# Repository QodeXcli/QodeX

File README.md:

# QodeX — the coding agent that stays on your side of the glass

Most agent CLIs are a rented brain with a terminal skin. QodeX is the opposite: a **local-first agentic coding CLI** that treats *your* machine as the source of truth. Qwen3-Coder on Ollama / LM Studio by default. Claude / GPT / Gemini / DeepSeek only if you invite them. Your repo does not become someone else's training set.

It does not just *chat about* code. It reads, edits, tests, and — if you ask — ships. And when you are not at the desk, it does not get the keys to the whole Mac: **shell can run in a Docker sandbox**, and **`--profile cloud`** is one switch between "think local" and "think in the cloud, execute in a box."

> Looking for an **LLM agent**, a **CLI agent**, or an **autonomous terminal agent** that can go fully offline? That's QodeX.

```bash
curl -fsSL https://raw.githubusercontent.com/QodeXcli/QodeX/main/install.sh | bash
qodex setup && qodex
```

**Version 2.33.0** · 100+ tools · self-improving · phone-driveable · English & Persian · Apache-2.0

---

## Highlights

- **Local-first & private** — runs entirely on *your* models (Qwen-Coder via Ollama / LM Studio); your code never leaves the machine. Claude / GPT / Gemini / DeepSeek are opt-in cloud fallbacks.
- **A desk on this machine, not a rented computer** — `qodex desk` is a local team of up to six that can run at once and share `~/.qodex/desks/computer`. A goal that would send, spend, delete, publish, or touch a secret waits for `qodex desk allow`. If the run then tries that call, the sentinel pauses the exact tool until `qodex desk allow-call`, and then it runs. Click and type work on macOS, on Linux with xdotool, and on Windows via PowerShell. `qodex desk teach --from-last` saves the tools the run actually used. [docs/DESK.md](docs/DESK.md).
- **One process you leave up** — `qodex up` fires schedules, drains runnable desks, seals a skill only when its witness patch still passes the real checker (no model), and attaches the chat bots you already configured. `qodex up status` says whether that pid is alive. `--once` is a single pass and does not open bots.
- **Named desktop controls** — `computer_use_tree` reads the OS accessibility tree (macOS AX, Windows UI Automation, Linux AT-SPI). `computer_use_invoke` presses one named control, refuses zero or two matches, and reads the tree again. If the control still looks the same, the result is unverified. A missing backend is an error, not a fake click.
- **Desktop shell** — `qodex desktop` prefers a native OS window (`native/`, built with `qodex desktop --build-native`). That window is not a browser. If the binary is missing it says so and falls back to Chrome/Chromium/Edge `--app`, or a tab. Loopback only. You read the real control tree, press or fill one name, and take a screenshot. It does not call a model.
- **Cloud browser, your account** — `qodex mcp add browserbase` connects to Browserbase's hosted server. The API key stays in the environment. `start` and `act` ask every time, because a session is billed and a click can submit. No key, no browser — the call errors.
- **`--profile studio` / `--profile cloud`** — named overlays, not a second product. Local Qwen on the Mac Studio in one file; a cloud model + Docker-isolated shell in another. `-p` is still `--print`.
- **Shell in a box, not on bare metal** — `runtime.backend: docker` bind-mounts the project and drops host `$HOME`, `docker.sock`, privileged mode, and host networking. File edits stay in the repo (a coding agent that cannot touch files is a chatbot). The Mac outside `/workspace` stays out of reach.
- **Guardrails around the model, not just prompts** — a syntax gate, completion gate, and per-language auto-verification run *around* the agent loop, so even a weak local model **can't ship broken or unverified code**.
- **It gets sharper the more you use it** — a real self-improvement loop captures the winning approach from *objectively-successful* tasks as quarantined skills. An **independent judge model** can promote them when you have a second model. On one local model (the default), **witnessed replay** re-applies the exact diff in a clean worktree and lets the compiler decide — `qodex skill witness`, no self-grade. **UCB1 A/B-tests** champion vs. challenger versions, **episodic memory** recalls how you solved similar tasks before, and it **learns from recurring failures**. It never overwrites a skill you wrote. Gap vs Hermes Agent: [docs/VS-HERMES.md](docs/VS-HERMES.md).
- **Always reachable — drive it from your phone** — run QodeX as a **Telegram / Discord / Slack service** and command the *same* agent from chat: stream tasks, approve diffs as inline buttons, and get **Living Artifacts** back as cards with an AI **vision review** (looks-good / needs-work / broken) and Approve / Edit / Reject.
- **Remembers across sessions** — a layered, **local** memory (curated `QODEX.md` rules · scoped project/user facts · per-project worklog · episodic task-recall · resumable sessions) with a **human-readable Markdown mirror** you can edit and git-commit, and a **budget-aware Light Memory Mode** for small context windows. The agent builds real context about *you* and *this* codebase instead of starting every session cold.
- **Live, shareable artifacts + a project dashboard** — build a page / React app / dashboard that **hot-reloads on every edit and auto-opens in your browser**; share it over your LAN or a private, token-protected https tunnel. `qodex dashboard` renders a live snapshot of providers, sessions, token/cost, memory, and skills.
- **Design and account connectors** — **Canva** and **Figma** were already one command. 2.12 adds the official Google servers (Gmail, Drive, Calendar, Docs, Sheets), Hotmail / Outlook, Notion, and Jira / Confluence. Each one is the vendor's real server. Nothing is simulated.
- **100+ built-in tools** — Tree-sitter code-graph, real Playwright browser automation, dev-servers, web search, vision, Docker / DB / WordPress, and any MCP server.
- **Persian-first** — prompts, skill matching, *and* generated artifact copy follow your chat language, not a fixed default.
- **Token-efficient** — sub-agent delegation, result-aging, compaction, and tool-gating keep the working context small on long sessions.

---

## Always-on, and it compounds

An "autonomous 24/7 agent" is easy to *say* and hard to *mean* — most of the time it's a chatbot wrapped in a cron job. QodeX's always-on story is three systems that actually exist, that you can read in this repo, and that each have tests:

- **Reachable any time** — the **transport-agnostic bot gateway** runs as a persistent service, so the agent is one message away from your phone. One turn per chat at a time (no interleaving), permission prompts as inline buttons, **deny-by-default auth**. ([Telegram / Discord / Slack](#telegram--discord--slack-bot))
- **Improves between sessions, on its own** — capture → **independent-judge** promotion → **UCB1** version A/B → **episodic recall** → **failure-lesson** injection. The loop is gated on *objective* success signals, not the model's self-grade, and a new **code-graph "fit" signal** grounds the judge in *your* codebase. ([Self-learning skills](#self-learning-skills))
- **Runs while you sleep — verifiably** — a built-in **cron scheduler** (launchd / crontab) runs tasks unattended and delivers the result to your phone. The headline recipe, **Autonomous Verified PR**, works on a sandbox branch, **verifies**, and opens a PR *only if it passed* — per-task **budget caps**, a **circuit breaker**, the **git sandbox**, and the guardrail gates all run too, so a 3am run **can't quietly ship broken code or melt your token budget**. ([Scheduled & autonomous](#scheduled--autonomous--the-real-247))

We're not going to claim a model thinks for you around the clock. We built the parts that make *unattended, repeated, real* work trustworthy — and we'd rather show the code than the slogan.

---

## What makes it different

Most agentic CLIs *delegate to the model* — they hand the model tools and trust it to use them well. That works with a frontier model and falls apart with a weaker local one (loops, half-finished edits, "done" when nothing was tested).

QodeX takes the opposite stance: **protect the model.** A layer of deterministic guardrails runs *around* the loop so even a smaller local model produces trustworthy output:

- **Syntax gate** — every edit is parsed before it's written; broken syntax is rejected, not saved.
- **Completion gate** — the model can't claim "tests pass" or "I fixed it" unless a test actually ran / an edit actually succeeded. Unsupported claims get bounced back for correction.
- **Auto-verification** — after the model thinks it's done, QodeX detects the project type and runs the real checker (`tsc`, `eslint`, `ruff`, `pyright`, `go vet`, `cargo`, `php -l` …) on touched files and force-feeds any errors back.
- **Interactive edit approval** — see a red/green diff and Accept / Edit / Continue / Reject before anything hits disk (or `/auto on` to skip).
- **Git-backed sandbox** — risky work runs on a hidden branch with checkpoints; auto-snapshot (`git stash`) before destructive commands, one command to roll back.
- **Process sandbox (Docker)** — a second, different isolation: the *shell* runs in a container so a remote-ish turn cannot `rm` your home directory. Pair it with `--profile cloud`. Not a Hub client — Hub is for approvals; this is where commands actually execute.
- **Skill security scanner** — skills installed from GitHub are scanned for prompt injection, secret exfiltration, destructive shell, and hidden-unicode payloads *before* they touch disk.

The result raises the **floor** (what a weak model is allowed to ship) without needing a bigger model.

## Token efficiency

Long agent sessions burn tokens on a growing history, not the (cached) system prompt. QodeX keeps the working context small with four real levers:

- **Delegation** — heavy file-exploration runs in a read-only sub-agent (`task`) with a *separate* context window; only its summary returns, so dozens of reads never pile up in the main window.
- **Result-aging** — stale large tool outputs are stubbed after a few turns (re-read on demand).
- **Compaction** — history is structured-summarized as the window fills.
- **Tool-gating** — only relevant tool schemas are sent each turn (a greeting sees ~20 tools, a real task ~50, out of 100+).
- **Opt-in `context.efficient: true`** tightens all of the above for weak local models — a **sliding token window** that compresses large tool outputs the very next turn.

### Hierarchical cache engineering

Standard agent caching pins only the static system block. QodeX goes further with a **multi-tier rolling-breakpoint** cache (Anthropic, on by default), so the part that actually grows — the conversation — is cached too:

- **Immutable tier** — core instructions + 70+ tool schemas, byte-identical across *every turn of the session*. A static/volatile boundary splits the system prompt so this core gets its own breakpoint and stays a cache **hit** the whole conversation — not just within one task.
- **Ephemeral / rolling tier** — per-turn injections (memory, retrieval, dir-tree) and the conversation history, pinned with a **breakpoint that advances every turn**.

In a deep agentic loop the re-sent prefix dominates each call, and it's now served at **0.1×** instead of full price — **up to ~90% off the input cost of every iteration after the first** (the `C × N` blow-up, defused) — with no loss of granular state and no shrinking of the context window. Caching the *growing history*, not just the system block, is the lever; opt out with `providers.anthropic.useCaching: false`.

A live `12.4k/200k ████░░░░░░ 8%` meter in the status bar shows how full the context window is.

## What it can do

Give QodeX a task in natural language (English or Persian) and it drives a real agent loop:

- **Read and edit code** — `read_file`, `write_file`, `edit_text`, `edit_symbol` (AST-aware), `multi_edit` (single-file sequential), `multi_file_edit` (atomic across up to 50 files).
- **Understand a codebase** — `ls`, `glob`, `grep`, plus a Tree-sitter code-graph: `project_overview`, `analyze_impact`, `find_callers`, `find_references`, `find_dead_code`, `safe_rename`.
- **Run commands** — `shell` on the host, or inside Docker when `runtime.backend: docker`; plus `code_run` for sandboxed Python / Node / TS / PHP / Ruby (macOS `sandbox-exec` where available).
- **Drive a real browser** — Playwright-backed Chromium: navigate, click, fill, screenshot, evaluate JS, read console + page errors — to verify your own UI changes. Click, fill, and page script ask every time. A standing yes does not cover them.
- **Manage dev servers & jobs** — `dev_server_start npm run dev` then `browser_navigate http://localhost:5173`; `background_job_start` for async work, all in one session.
- **Search the web** — DuckDuckGo by default (hardened with a `lite` fallback + retry), or Tavily / Brave / **Firecrawl** (returns full page markdown inline to save round-trips) when you set a key. Auto-fallback chain across whatever keys are present.
- **Smart vision** — `vision_analyze` automatically uses *your own* vision-capable model (Gemini, GPT‑4o, Claude, or a local Qwen‑VL) when your primary or sub‑agent can already see; it only spins up a dedicated vision model when neither can.
- **Shareable live artifacts** — build a web page / React / dashboard and serve it with `artifact_live` that **hot‑reloads on every edit and auto‑opens in your browser** so you watch it change live; `share="network"` opens it to your LAN and `share="tunnel"` gives a **private https link your team can open** (token‑protected) — a live PR walkthrough or project dashboard.
- **Design integrations (Figma + Canva)** — `qodex mcp add figma` (3 ways: your logged‑in desktop Dev Mode, a personal token, or hosted OAuth) and `qodex mcp add canva` (OAuth login) let the model turn a Figma frame into code or build a Canva design — driven from the terminal over MCP.
- **Google, Hotmail, Notion, Jira** — `qodex mcp add gmail` (also `google-drive`, `google-calendar`, `google-docs`, `google-sheets`), `hotmail`, `notion`, `atlassian`. Google's servers are the official `*mcp.googleapis.com` endpoints. They are a developer preview: you create the OAuth client (marked "Use this client for an AI-powered agent") and export `GOOGLE_OAUTH_CLIENT_ID` / `GOOGLE_OAUTH_CLIENT_SECRET`. Gmail's server searches and drafts; it does not send. Hotmail is `@softeria/ms-365-mcp-server` in personal mode (device code). Work tenants are `outlook-work`. Canva was already `qodex mcp add canva`.
- **Matches your code style automatically** — QodeX infers the project's conventions (indentation, quotes, semicolons, naming) from its own source + `.editorconfig` and writes new code to match, **without you having to configure or `remember` anything**. Off via `context.styleProfile: false`.
- **Self‑learning skills** — after a task that *objectively* succeeded (verified + honest, ≥ a few tool calls), QodeX can capture the winning approach as a **candidate** skill in quarantine. An **independent judge model** (a *different* model from the one that did the work) reviews it before it’s promoted, and a human‑authored skill is **never** overwritten. Drive it with `qodex skill candidates | curate | promote`. Off by default (`learning.enabled`).
- **Trade‑off & business analysis** — ask it to analyze or plan (not code) and it produces **decision‑grade output**: options × weighted criteria → a scored comparison and one clear recommendation, business‑plan structure, no invented numbers.
- **Persian‑first** — skill auto‑loading and tool selection understand Persian prompts (تحلیل، دیتابیس، آرتیفکت…), not just English keywords.
- **Verify its own work** — `auto_fix` runs your test command in a fix→test loop with an iteration cap and same-failure-twice detection; the auto‑verify gate runs the right checker **per language** in a polyglot repo (TS *and* Python both get checked).
- **Git** — status, diff, log, branch, commit, create-pr, release-notes.
- **Skills** — install from a curated registry or any GitHub repo (single / multi / catalog), security-scanned on the way in; `search_skills` to find them.
- **Sub-agents & orchestration** — `task` delegates to a separate model/window; `orchestrate` runs a DAG of sub-agents; `gather` fans out reads in parallel.
- **MCP** — connect any MCP-compatible server; its tools join the same registry as built-ins.
- **Live control dashboard** — `qodex dashboard` (alias `dash`) opens a **local, token-protected control panel** (127.0.0.1 only) that doesn't just *show* your QodeX — providers, sessions, token/cost, memory, skills — it **drives** it: toggle prompt caching / efficient mode / memory mode / sub-agents / learning, enable·disable·remove **scheduled tasks**, forget a memory fact, and apply MoE **offloading** — changes hit your real config and stores. Every capability is one entry in an action registry, so the panel grows to cover all of QodeX. `--static` writes the old read-only HTML snapshot.
- **Add a provider by just asking** — tell QodeX *"add Groq with my key"* and the `add_provider` tool wires the gateway into `~/.qodex/config.yaml` (key stays in `~/.qodex/.env`, never the config); or run `qodex provider add` for a guided setup. Unknown providers are refused unless you give a base URL + key-env, so nothing is silently misconfigured.
- **Domain tools** — Docker, databases, WordPress (`php -l` linting), media (ffmpeg), frontend/print, OpenAPI digest, and more.

## Self-learning skills

QodeX can **learn reusable playbooks from your successful tasks** — without the usual failure mode of an agent rubber-stamping its own work and overwriting your hand-tuned skills. The whole loop is **off by default** and gated on *objective* signals, not the model's self-grade.

**How it works:**

1. **Capture** — when a task finishes in the git sandbox and *objectively* succeeds (it compiled / type-checked, the completion-claim gate passed, and it took at least a few tool calls and changed a file), QodeX distills the winning approach into a `SKILL.md` and assigns it a **confidence score (0–100)** from those objective signals.
2. **Quarantine** — the new skill is written to `~/.qodex/skills-candidates/` (a dir QodeX never auto-loads), stamped `provenance: machine`, `status: candidate`. It can't affect the model until promoted.
3. **Independent review** — `qodex skill curate` runs an **independent judge model** (a *different* model from the one that did the work — a self-grade is refused) against a fixed rubric (reusable / correct / specific / non-redundant). The judge is **grounded in your codebase**: a Tree-sitter **code-graph "fit" signal** checks how many of the symbols a candidate references actually exist here, so a skill that name-drops APIs your project doesn't have scores lower (and the capture notice shows it: *"confidence 82/100 · codebase-fit 90%"*). Near-duplicate candidates are **merged** into one. It **never overwrites a human-authored skill**, and snapshots the skills dir (`tar.gz`) before any change so you can roll back.
4. **Auto-evaluation** — `qodex skill eval <name>` (or `learning.autoEval` to run it right after capture) **replays the skill's original task in a throwaway git worktree** and runs the **real** verifier (`tsc`/`ruff`/…) on the code it produces, recording **pass / fail / inconclusive** into the skill. It tests whether the skill actually *works*, not just whether a judge likes it. Content-hash cached.
5. **Learning from failures** — with `learning.failureLessons.enabled`, QodeX records tool failures and, once a mistake **recurs across tasks**, injects a deterministic "learned caution" into the prompt (e.g. *"verify a symbol exists before `edit_symbol`"*) so it stops repeating it. One-offs never teach; see `qodex skill lessons`.
6. **Episodic memory** — with `learning.episodicMemory.enabled`, QodeX records a lean episode after each successful task and, at the start of a new one, recalls **similar past tasks on this project** and injects a one-line reminder of what worked — so it reuses its own approach instead of rediscovering it. Retrieval is **smart, not noisy**: an unrelated task recalls nothing, and the top-K are selected for **relevance *and* diversity** (MMR — so a recurring task doesn't inject K copies of itself), **grounded** against the current tree (episodes pointing at files that no longer exist are demoted, like the skill-judge's codebase-fit), with a **recency tie-break** toward your more recent solution.

QodeX also **auto-matches your code style** (indentation, quotes, semicolons, naming — inferred from the project + `.editorconfig`) so generated code blends in without you having to spell it out. Off via `context.styleProfile: false`.

```yaml
# ~/.qodex/config.yaml — opt in
learning:
  enabled: true                     # capture candidates after successful tasks
  minToolCalls: 5                   # how substantial a task must be to capture
  judgeModel: llama-3.3-70b-versatile   # the INDEPENDENT judge (must differ from defaults.model)
  autoPromoteMinConfidence: 50      # hold lower-confidence captures for human review
  autoEval: false                   # run `skill eval` automatically after each capture
  failureLessons:
    enabled: true                   # learn from RECURRING tool failures
  episodicMemory:
    enabled: true                   # recall similar past tasks and reuse what worked
    topK: 2                         # how many past episodes to inject
    diversity: 0.3                  # 0–1: keep the top-K distinct, not K clones of one task
```

**A worked example.** With `learning.enabled` + an independent `judgeModel`, a typical loop:

```text
> add cursor pagination to the /orders endpoint        # you give a task
… QodeX edits, type-checks, tests, and the sandbox merges (objective success) …
🎓 Captured candidate skill "add-cursor-pagination" (confidence 82/100)
🧪 Auto-eval of "add-cursor-pagination": pass            # (if learning.autoEval)

$ qodex skill candidates        # review the quarantined capture
$ qodex skill curate            # an INDEPENDENT judge promotes/merges the good ones
$ qodex skill stats             # captured 3 · promoted 2 · promotion rate 67%

# next week, a similar task:
> add pagination to the /users endpoint
# → QodeX recalls the past episode + loads the promoted skill automatically.
```

```bash
qodex skill candidates          # list quarantined captures (with confidence)
qodex skill curate              # independent judge merges + promotes the good ones
qodex skill eval <name>         # replay the skill in a clean worktree + real verify → pass/fail
qodex skill promote <name>      # promote one yourself (you are the independent reviewer)
qodex skill reject <name>       # discard a candidate
qodex skill stats               # learning metrics: captured / promoted / merged, promotion rate, avg confidence
qodex skill lessons             # cautions learned from your recurring failures
qodex skill snapshots           # rollback points;  qodex skill restore <archive>  to roll back
```

> Every successful task can also be exported as a **ShareGPT JSONL** corpus (`flywheel.datasetExport: true` → `~/.qodex/dataset/`) — a ready-to-use dataset for a future zero-cost local fine-tune. Strictly local; nothing is uploaded.

### Skill versioning & A/B testing (UCB1)

A skill keeps its whole history in **one flat directory** — `manifest.json` + `SKILL.v1.md`, `SKILL.v2.md`, … — no symlinks, identical on every OS. When a new candidate is captured for an existing skill it becomes a **challenger** to the stable **champion**, and QodeX routes traffic between them with the **UCB1 adaptive bandit** instead of a fixed split: it explores the challenger enough to get signal, then favours whichever has the higher score — and a challenger that turns out worse has its traffic driven to **zero automatically**.

The score is a **composite reward**, not just win-rate: *success* dominates, but *token-* and *time-efficiency* (normalized **relative to the champion**) break ties — so between two equally-correct versions, the **cheaper, faster** one wins.

```yaml
learning:
  versioning:
    strategy: ucb1                 # or 'champion-only' to freeze a sensitive skill (UCB off)
    ucbExplorationFactor: 1.41     # √2 — higher explores challengers more
    minChallengerTrials: 5         # force a challenger ≥5 runs before judging it
    rewardWeights: { success: 0.7, token: 0.15, time: 0.15 }
```

```text
$ qodex skill versions git-commit-expert
Skill "git-commit-expert"  ·  strategy: ucb1  ·  routed this turn → v2

  v1  [human]   ★ champion
      success: 88% over 40  ·  tokens: 60000  ·  1900ms/run  ·  confidence: 75
      UCB: reward 0.838 + bonus 0.214 = 1.052
  v2  [machine] ⚡ challenger
      success: 92% over 12  ·  tokens: 41000  ·  1300ms/run  ·  confidence: 60
      UCB: reward 0.921 + bonus 0.391 = 1.312     ← higher → gets this turn

$ qodex skill rollback git-commit-expert v1     # snap the champion back to v1 anytime
```

## Memory & continuity

Most CLI agents are amnesiac — every session starts from a blank slate and you re-explain the same things. QodeX **remembers**, across five layers that each answer a different question, so a model on *your* machine accumulates real context about you and your codebase over time:

| Layer | Answers | Where it lives | Author |
|---|---|---|---|
| **Curated rules** | "What are the rules here?" | `QODEX.md` in the repo + `~/.qodex/QODEX.md` (global) | **you** — version-controlled, authoritative |
| **Learned facts** | "What did I learn about this codebase / this user?" | `session_facts` in `~/.qodex/sessions.db`, scoped `project` (per-cwd) or `user` (global) | the **agent**, mid-task |
| **Project worklog** | "What's been done here lately?" | `project_worklog` (per-cwd) | the agent + `/project log` |
| **Episodic memory** | "How did I solve a task like this before?" | `~/.qodex/episodes/*.jsonl` | the agent, after a *verified* success |
| **Sessions** | "Pick up exactly where we left off." | `sessions` + `messages` in `sessions.db` | every turn — `/resume <id>` |

The split is **deliberate**: *your* curated rules (`QODEX.md`, git-tracked) stay separate from the *agent's* auto-learned scratchpad (the DB) — no machine write ever touches your authoritative file, and there are no merge conflicts. Facts are **scoped** — a `project` fact (a build command, a gotcha) is auto-injected only when you start in that directory; a `user` fact (*"prefers Persian comments"*, *"always run tests before saying done"*) follows you into **every** project. Recall is smart, not heavy: episodic memory injects only relevant, **de-duplicated** past tasks above a threshold (an unrelated task recalls nothing) — a one-line reminder, never a full transcript.

**A Markdown mirror you can read, edit, and git-commit.** `/memory export` writes the agent's learned facts to a human-readable `MEMORY.md` (project) and `~/.qodex/memory.md` (user). Edit them by hand — fix a wrong fact, add three — and `/memory import` folds your changes back into the DB (additive). The DB stays the source of truth; the Markdown is the window into it.

**Light Memory Mode for small context windows.** On a roomy model, every fact is injected (`memory.mode: full`). On a tight local model, set `memory.mode: lightweight` (or `auto`) — QodeX injects your `!important`-tagged facts plus as many recent ones as fit a token budget, and leaves the rest to load on demand. Your memory doesn't shrink; only what's *pushed into each prompt* does.

**Searchable memory (FTS5).** As facts pile up, dumping the newest N isn't enough — `recall query="deploy key"` does a **relevance-ranked full-text search** (SQLite FTS5) over your facts and pulls out the specific one, so the agent finds an old gotcha instead of rediscovering it. This is the on-demand half of Light Memory Mode: lightweight mode keeps prompts small, and search retrieves anything it left out. The index stays in sync automatically and falls back to a substring scan if a build lacks FTS5.

```text
> the build here is `npm run build:prod`, not `npm run build`
🧠 remembered (project)              # silently re-injected next time you start in this dir

/memory                              # show what's stored for this project
/memory export                       # write the human-readable MEMORY.md mirror
/memory import                       # pull hand-edited facts from the markdown back in
/memory forget <substring>          # drop matching facts
/project        ·  /project log <e>  # this project's worklog (view · append)
/sessions       ·  /resume <id>      # list past sessions · rehydrate one
```

```yaml
# ~/.qodex/config.yaml — tune what gets pushed into each prompt (DB + mirror are unaffected)
memory:
  mode: auto              # full | lightweight | auto (lightweight on small context windows)
  injectMaxTokens: 2000   # budget for facts in lightweight mode (!important always included)
```

It all lives under `~/.qodex/` — **nothing is uploaded**, the same privacy line as your code.

## Two worlds, one flag

You should not rebuild your life to try a cloud model for an afternoon. Drop two YAML files in `~/.qodex/profiles/` and flip them like a light switch.

```yaml
# ~/.qodex/profiles/studio.yaml  — the Mac Studio, Qwen, zero egress
defaults:
  provider: ollama
  model: qwen3-coder
runtime:
  backend: local
```

```yaml
# ~/.qodex/profiles/cloud.yaml  — think in the cloud, execute in a box
defaults:
  provider: anthropic
  model: claude-sonnet-4-6
runtime:
  backend: docker
  docker:
    image: node:22-bookworm
    network: none
    memory: 2g
```

```bash
qodex --profile studio          # local model, host shell
qodex --profile cloud           # cloud model, Docker-isolated shell
qodex --profile cloud bot       # same box, now from Telegram
QODEX_PROFILE=cloud qodex
qodex profile list
qodex profile show studio
```

`-p` is `--print` (headless). Profiles are `--profile` / `QODEX_PROFILE` / `defaults.profile`. Merge order: built-in defaults → `~/.qodex/config.yaml` → project `.qodex/config.yaml` → **the overlay last**. A missing name is a hard error — you never silently stay on local while believing you are in the box.

The Docker runtime bind-mounts the project at `/workspace`. It does **not** mount `docker.sock`, does **not** pass host `$HOME`, drops every capability, and defaults `--network none`. If Docker is not installed you get `[SANDBOX_UNAVAILABLE]`, not a quiet fall-through onto bare metal.

That is the point of building the sandbox *before* another chat surface: when you are on the sofa and the agent wants to try a script, the script meets a container — not the rest of the Mac.

## Install

Thirty seconds. Then `qodex setup`. Then type a real task in the repo you already have open. If it reads `package.json` and tells you the truth, you are in.

### One line (macOS · Linux · WSL)

```bash
curl -fsSL https://raw.githubusercontent.com/QodeXcli/QodeX/main/install.sh | bash
```

Checks for **git + Node 20+** (installs Node via your package manager if it's missing or too old), clones QodeX to `~/.qodex-src`, builds it, and puts `qodex` and `qx` on your PATH. **Idempotent** — re-run it to update. Knobs: `QODEX_SRC_DIR`, `QODEX_BRANCH`, `QODEX_NO_LINK=1`; preview without touching anything via `QODEX_DRY_RUN=1`.

> Prefer to read before you pipe to `bash`? The script is [`install.sh`](install.sh) in this repo — or follow the manual steps below.

### Manual

**Prerequisites:** **Node 20+** (Node 22 LTS recommended) and **Git**. `dist/` is built locally (not committed), so the `npm run build` step is **required** on every platform. The build links two commands — `qodex` and the short alias `qx`.

### macOS

```bash
# Node + Git via Homebrew (or use nvm). Check: node -v  →  v20+  
brew install node git

git clone https://github.com/QodeXcli/QodeX.git qodex && cd qodex
npm install
npm run build
npm link            # puts `qodex` and `qx` on your PATH
```

### Linux

```bash
# Debian/Ubuntu — get Node 20+ from NodeSource if your distro ships an older one
curl -fsSL https://deb.nodesource.com/setup_22.x | sudo -E bash -
sudo apt-get install -y nodejs git
# (Fedora: sudo dnf install nodejs git    ·    Arch: sudo pacman -S nodejs npm git)

git clone https://github.com/QodeXcli/QodeX.git qodex && cd qodex
npm install
npm run build
sudo npm link       # or plain `npm link` if your npm prefix is user-writable
```

### Windows

Open **PowerShell** and install Node + Git (via [winget](https://learn.microsoft.com/windows/package-manager/), or the installers from [nodejs.org](https://nodejs.org) / [git-scm.com](https://git-scm.com)):

```powershell
winget install OpenJS.NodeJS.LTS Git.Git
# reopen PowerShell so PATH refreshes, then:
git clone https://github.com/QodeXcli/QodeX.git qodex; cd qodex
npm install
npm run build
npm link            # `qodex` and `qx` on PATH
```

> **Windows tip:** if the native `better-sqlite3` module fails to compile, install the C/C++ build tools (`npm install --global windows-build-tools`, run PowerShell as Administrator) — or use **WSL2** and follow the **Linux** steps above (recommended for the smoothest experience).

### Optional — browser automation (all platforms)

Playwright-backed Chromium for the `browser_*` tools (~200 MB, one-time):

```bash
npm install playwright
npx playwright install chromium
```

> Then run `qodex setup` to detect your local models and write `~/.qodex/config.yaml`.

## Updating to a newer version

**The easy way — one line (works no matter how you first installed):**

```bash
curl -fsSL https://raw.githubusercontent.com/QodeXcli/QodeX/main/install.sh | bash
```

The installer is **idempotent**: it pulls the latest `main`, rebuilds, and re-links `qodex`/`qx`. Re-running it **replaces your old version in place** — you don't need to uninstall anything first. At the end it checks that the `qodex` your shell runs is actually the fresh build, and if an older copy is still winning on your `PATH` it prints the exact one-line fix.

**From inside QodeX** (once you're on a build new enough to have it):

```bash
qodex update --check      # is a newer version available?
qodex update              # git pull → npm install → npm run build (then restart qodex)
```

**If you cloned manually into a folder** (e.g. `~/Downloads/qodex`) and want that folder updated:

```bash
cd ~/Downloads/qodex          # your existing clone
git pull                       # get the latest code
npm install && npm run build   # rebuild (dist/ is not committed — this step is required)
npm link                       # make sure `qodex` points here
```

**Coming from an old copy and just want a clean switch?** Delete the old clone and use the one-liner — it installs to `~/.qodex-src` and takes over the `qodex` command:

```bash
rm -rf ~/Downloads/qodex       # or wherever your old copy lives (safe: it's just source)
npm uninstall -g @qodex/cli 2>/dev/null; hash -r   # drop any stale global link
curl -fsSL https://raw.githubusercontent.com/QodeXcli/QodeX/main/install.sh | bash
```

**Verify which build is active** any time:

```bash
command -v qodex     # where the command resolves
qodex --version      # the version now running
```

> After updating, **restart QodeX** (and any running session) so the new `dist/` is loaded — the running process keeps the old build until it exits.

## Quick start

```bash
qodex setup          # detects local models, writes ~/.qodex/config.yaml
qodex                # or:  qx
> read package.json and summarize what this project does
```

Stuck between a local 32B and a cloud API? Don't rewrite config — `qodex --profile studio` vs `qodex --profile cloud`. Need the shell off the host? Put `runtime.backend: docker` in the cloud profile.

## Configuration

## Configuration

Lives in `~/.qodex/config.yaml`. A minimal local-model setup pointed at LM Studio:

```yaml
defaults:
  provider: openai
  model: qwen/qwen3-coder-next
  preferLocal: true

providers:
  ollama:
    baseUrl: http://localhost:11434
  openai:
    apiKeyEnv: OPENAI_API_KEY
    baseUrl: http://127.0.0.1:1234/v1   # point at LM Studio
    extraModels:
      - id: qwen/qwen3-coder-next
        contextWindow: 32768
        supportsToolCalls: true

roles:
  subagent:
    provider: ollama
    model: qwen3-coder      # smaller/faster model for delegated reads

context:
  efficient: false          # set true on weak local models to save tokens

subagents:
  mode: parallel            # off | sequential | parallel
```

### Large (MoE) models on limited VRAM + local "turbo cache"

Big Mixture-of-Experts coders (Qwen3-Coder-MoE, DeepSeek-MoE) don't have to fit entirely in VRAM — keep some layers on the GPU and the rest on the CPU via Ollama's `num_gpu`, which QodeX forwards verbatim:

```yaml
providers:
  ollama:
    keepAlive: 30m            # keep the model + its KV cache warm between turns — the local "turbo cache"
    options:
      num_gpu: 14             # layers on GPU; the rest run on CPU (lower = fits a bigger model)
      num_ctx: 32768          # KV-cache size; QodeX already defaults this to the model's window
```

Not sure what `num_gpu` to use? Let QodeX figure it out:

```bash
qodex offload                 # auto-detects VRAM (nvidia-smi / Apple unified memory) + the
                              # model's size & layer count from Ollama, and suggests a num_gpu
qodex offload --apply         # …and writes it to providers.ollama.options.num_gpu
qodex offload --vram 12       # override the VRAM budget if auto-detect is off
```

e.g. a 48 GB MoE on a 12 GB GPU → *keep ~14/64 layers on the GPU, the rest on CPU*. (The pure core is `suggestGpuLayers` in `src/llm/offload.ts`.)

Two things make local fast here: **`keep_alive`** keeps the model resident so there's no cold reload, and QodeX's **byte-stable prompt prefix** (hierarchical cache work above) means the engine's **KV prefix cache hits** instead of re-prefilling the whole context every turn — the local counterpart to Anthropic prompt caching.

**Run the model on another box — `qodex tunnel`.** Local-first answer to remote backends: SSH-forward to a workstation running Ollama/LM Studio and drive it from your laptop, code and execution staying local.

```bash
qodex tunnel --host workstation --user me --remote-port 11434 --local-port 11434
# → point providers.ollama.baseUrl at http://localhost:11434; the 70B/MoE model runs over there.
```

Cloud providers are opt-in. Web-search keys are read from the environment, never the config file:

```bash
export TAVILY_API_KEY=tvly-...
export BRAVE_SEARCH_API_KEY=...
export FIRECRAWL_API_KEY=fc-...          # set FIRECRAWL_SCRAPE_CONTENT=1 for inline markdown
```

## Built-in tools

100+ tools across these areas — run `/tools` inside QodeX for the full list with descriptions:

| Area | Examples |
|---|---|
| **Filesystem** | read_file, write_file, edit_text, edit_symbol, multi_edit, multi_file_edit, ls, glob, grep |
| **Shell & code** | bash, code_run |
| **Code graph** | project_overview, analyze_impact, find_callers, find_references, find_dead_code, safe_rename, semantic_search |
| **Diagnostics** | type/lint checkers (tsc, eslint, ruff, pyright, go vet, cargo, php -l) |
| **Git** | status, diff, log, branch, commit, create_pr, release_notes |
| **Web** | web_search (DuckDuckGo / Tavily / Brave / Firecrawl), web_fetch, network_check |
| **Browser** | navigate, click, fill, screenshot, console, evaluate, get_text, wait_for |
| **Dev server / jobs** | dev_server_start/stop/log, background_job_start/status/wait/cancel |
| **Skills** | use_skill, search_skills, install_skill (security-scanned) |
| **Memory** | remember, recall, forget (project/user-scoped, local) |
| **Sub-agents** | task, orchestrate, gather, present_plan, todo_read/write, auto_fix |
| **Vision** | vision_analyze |
| **Domain** | Docker, database, WordPress, media (ffmpeg), frontend/print, OpenAPI |
| **MCP** | connect any MCP server; its tools join the registry |

## Slash commands

```
/help              Overview
/network           Diagnose internet + Ollama + LM Studio connectivity
/tools [--all]     List registered tools by category
/plan  /normal     Plan mode (read-only)  /  back to normal
/auto on|off       Auto-approve permissions
/model <id>        Override model for this conversation
/subagents off|sequential|parallel
/snapshot list|take|restore        Manage auto-snapshots
/cost  /tokens     Token / cost usage
/insights          Token / tool / latency breakdown
/index [--force]   Build/refresh the code graph
/mcp               List connected MCP servers
/memory [export|import|forget <s>|clear]   Learned facts — show · mirror to MEMORY.md · import edits · drop · wipe
/project [log <e>] This project's worklog — view, or append an entry
/sessions  /resume <id>  /clear  /exit
```

Plus any custom commands you drop in `.qodex/commands/` as markdown.

From the shell: `qodex sessions list|show <id>|export <id>|search <query>`. Safe shell that should skip the approval hub: `execution.allow` in `config.yaml` (`git status`, `npm test`, …).

## End-to-end example

```
> add a logout button to the navbar in src/Header.tsx and verify it works
```

QodeX will: read `Header.tsx` → add the button (shown as an approvable diff) → `dev_server_start npm run dev` → `browser_navigate` localhost → click the button → check the console for errors → screenshot → `vision_analyze` to confirm it looks right → run the type-checker on the touched file → stop the server and report. One agent loop, with the guardrails above running throughout.

## Telegram / Discord / Slack / WhatsApp / Signal

Drive the same agent from chat — stream tasks to QodeX from your phone. New platforms are **thin Transports** on the same gateway (and the same Operator Hub lanes). They are not a second agent, and they do not scrape unofficial clients.

```bash
# 1. put the token(s) in ~/.qodex/.env (secrets never go in config)
echo 'TELEGRAM_BOT_TOKEN=123:abc' >> ~/.qodex/.env
#   Slack uses Socket Mode (no public URL needed) and TWO tokens:
#   echo 'SLACK_APP_TOKEN=xapp-...' >> ~/.qodex/.env
#   echo 'SLACK_BOT_TOKEN=xoxb-...' >> ~/.qodex/.env
#   WhatsApp Cloud API (official Graph + webhook — not WhatsApp Web):
#   echo 'WHATSAPP_TOKEN=...' >> ~/.qodex/.env
#   echo 'WHATSAPP_PHONE_NUMBER_ID=...' >> ~/.qodex/.env
#   echo 'WHATSAPP_VERIFY_TOKEN=pick-a-string' >> ~/.qodex/.env
#   echo 'WHATSAPP_APP_SECRET=...' >> ~/.qodex/.env   # required — POST HMAC; verify token is GET-only
#   Signal via your own signal-cli daemon (no unofficial phone clone):
#   echo 'SIGNAL_ACCOUNT=+15551234567' >> ~/.qodex/.env
#   # signal-cli -a +15551234567 daemon --tcp 127.0.0.1:7583
#   Matrix Client-Server API (your homeserver, your access token — not E2EE):
#   echo 'MATRIX_HOMESERVER=https://matrix.example' >> ~/.qodex/.env
#   echo 'MATRIX_ACCESS_TOKEN=syt_...' >> ~/.qodex/.env
#   Email is IMAP + SMTP on your server (not a webmail login):
#   echo 'EMAIL_FROM=me@example.com' >> ~/.qodex/.env
#   echo 'IMAP_HOST=imap.example.com' >> ~/.qodex/.env
#   echo 'IMAP_USER=me@example.com' >> ~/.qodex/.env
#   echo 'IMAP_PASSWORD=...' >> ~/.qodex/.env
#   echo 'SMTP_HOST=smtp.example.com' >> ~/.qodex/.env

# 2. enable the platform + allowlist your user id (deny-by-default) in config
#    bot:
#      telegram: { enabled: true, allowedUsers: ["<your-telegram-id>"] }
#      discord:  { enabled: true, allowedUsers: ["<your-discord-id>"] }   # needs: npm i discord.js
#      slack:    { enabled: true, allowedUsers: ["<your-slack-user-id>"] } # needs: npm i @slack/socket-mode @slack/web-api
#      whatsapp: { enabled: true, allowedUsers: ["15551234567"] }          # digits, no +
#      signal:   { enabled: true, allowedUsers: ["+15551234567"] }
#      matrix:   { enabled: true, allowedUsers: ["@you:matrix.example"] }
#      email:    { enabled: true, allowedUsers: ["you@example.com"] }

# 3. run it from the project directory you want it to work in
#    Prefer --profile cloud + runtime.backend: docker so a sofa-command cannot rm ~
qodex bot                 # all enabled platforms
qodex bot --whatsapp
qodex bot --signal
qodex bot --matrix
qodex bot --email
```

WhatsApp Cloud API needs a **public HTTPS webhook** (Cloudflare Tunnel / `qodex tunnel`) pointed at `http://127.0.0.1:8787` (`WHATSAPP_WEBHOOK_PORT`). Signal talks to **your** `signal-cli` over JSON-RPC — we never log in as you on a third-party server. Matrix talks to **your** homeserver with the Client-Server API (`/_matrix/client/v3`). The first sync is only a cursor, so old history is not replayed. Encrypted rooms are skipped, not claimed as read. Email talks to **your** IMAP and SMTP servers. The first poll only stores `UIDNEXT`, so mail already in the box is not answered and not marked read. A stream of edits becomes one letter. Cleartext is refused except to localhost.

One transport-agnostic gateway does all the work; the platform adapters are thin — **Telegram** and **WhatsApp Cloud** need zero extra npm packages, **Discord** / **Slack** are optional lazy-loaded deps, **Signal** needs a local `signal-cli` daemon. Adding a platform is one adapter implementing the same `Transport` seam, so behaviour never drifts between them.

**Talk to it — voice memos.** Send a Telegram voice message and QodeX transcribes it and runs it as your turn (it echoes `🎙️ "…"` so you can see what it heard). Local-first, like web-search and vision: point `QODEX_TRANSCRIBE_CMD` at any local STT (whisper.cpp, faster-whisper, a script — `{file}` is the audio path, STDOUT is the transcript) for a fully-offline path, or set `OPENAI_API_KEY` for the cloud fallback. Neither configured ⇒ a friendly "just type" note, never a crash. The bug-classes that wreck chat-agent UIs are each solved once: **throttled, coalesced streaming** with code-fence-aware spill across messages (no edit-flood / no sheared code blocks), **one turn per chat at a time** (later messages queue — no interleaving), **permission prompts as inline buttons** (tap or reply), and **deny-by-default auth** (a coding agent runs shell on your host, so an empty allowlist admits no one; `"*"` opts into public access deliberately).

**Full agent control from your phone.** Commands live in one declarative registry, so every command is also pushed to the client as a **native `/` menu** (tap-to-pick, with descriptions) — no memorizing:

| Command | What it does |
|---|---|
| `/help` | every command, generated from the registry |
| `/new` | fresh conversation (new session) |
| `/stop` | abort the running task |
| `/status` | running/queued · model · project · session · auto state |
| `/auto on \| off` | auto-approve actions (skip the buttons) — handy on mobile, off by default |
| `/model [id]` | show or switch the model for this conversation |
| `/sessions` · `/resume <id>` | list past sessions and continue one (same store as the CLI) |
| `/episodes` | past tasks solved here, from episodic memory |
| `/impact <symbol>` · `/rename <old> <new>` | code-graph shortcuts — blast-radius of a symbol · AST-safe rename (with approval) |

Adding a command is **one entry** — Telegram, Discord, Slack, WhatsApp, and Signal all gain the command and its `/help` line. Capabilities a given build doesn't support degrade to a friendly note, never a crash. WhatsApp reply-buttons (max 3) and Signal numbered replies both resolve through the same hub `answer(id)`.

**Living Artifacts in chat — with an AI vision review.** Ask for a dashboard, a landing page, or a chart from your phone and QodeX doesn't dump code at you — it builds a **versioned artifact**, renders it, and (for web types) runs a **vision self-review** that actually *looks* at the result and verdicts it **LOOKS_GOOD / NEEDS_WORK / BROKEN**, listing concrete issues. You get back a compact **card**:

```text
📊  Sales dashboard  ·  html · v3
🔎  vision review: NEEDS_WORK
    • legend overlaps the Q4 bars
    • contrast too low on the dark header
[ ✅ Approve ]   [ ✏️ Edit ]   [ ❌ Reject ]   [ 🔗 Open live ]
```

Tap **Edit** and reply with the change in plain language; tap **Open live** for the hot-reloading, token-protected https link. The agent iterates create → preview → review → fix until the vision check passes — the same loop the CLI runs, now driven from chat.

## Scheduled & autonomous — the real "24/7"

Plenty of agents *say* "autonomous 24/7." QodeX has a plain, boring scheduler that actually does it — and, crucially, **runs every unattended job through the same guardrails as an interactive one**, so leaving it running can't quietly ship broken code.

A built-in cron (5-field expressions + `@daily`/`@hourly`/… aliases) installs as a **macOS LaunchAgent** or a **Linux crontab** line, ticks every minute, and runs each due task as an **isolated headless process** (file-locked, 30-min hard cap, per-run logs under `~/.qodex/schedule-logs/`).

```bash
qodex schedule install                       # macOS launchd / Linux crontab — runs the tick every minute
qodex schedule add --name nightly-deps \
  --cron "@daily" \
  --prompt "check for outdated deps and summarize what changed" \
  --deliver telegram:<your-chat-id>          # result lands on your phone, not just a desktop ping
qodex schedule list      ·  runs <id>  ·  enable/disable <id>  ·  rm <id>
```

**Deliver results to chat.** `--deliver telegram:<chatId>` (or `discord:<channelId>` / `slack:<channelId>`) posts each run's outcome to your phone — the scheduler talks to the platform REST API directly, so it needs no running bot. A recipe's verdict line leads the message.

**Autonomous *Verified* PR — the differentiator.** `--recipe verified-pr` doesn't just run a prompt; it wraps your goal in an unattended-safe **protocol**:

> work on a fresh **sandbox branch** → make the change → **run the tests + per-language verifiers** → and **open a PR only if verification actually passed**. If it fails, it opens *nothing*, claims *nothing*, and reports exactly what broke.

```bash
qodex schedule add --name nightly-flaky-fix \
  --cron "0 3 * * *" \
  --recipe verified-pr \
  --prompt "find and fix flaky tests in this repo" \
  --deliver telegram:<your-chat-id>
# 3am: works on a branch, verifies, and either DMs you "VERIFIED-PR: opened <url>"
#      for your morning review — or "VERIFIED-PR: blocked — <reason>". Never a false green.
```

That's the honest version of an always-on agent: it works while you sleep, but the completion gate, auto-verification, and git sandbox run too — so what reaches you is a PR you can trust, not a confident lie. See it as a one-page story: `qodex maintain-demo`.

**`--recipe maintain` — a codebase that improves itself.** The self-improving loop, built on the moat. Each **scope** is a conservative, *provable* cleanup shipped through the verified-PR protocol above — opt-in, and every run lands in the dashboard's receipts panel (tagged with its scope):

- **`dead-code`** (default) — code-graph finds *one* provably-unused item (`analyze_impact`/`find_references` → zero references or it blocks), removes only that.
- **`unused-imports`** — removes import bindings referenced zero times in their file (proven via the linter / `tsc --noUnusedLocals`); never touches side-effect imports.
- **`unused-locals`** — removes unused `const`/`let` bindings, with an extra **side-effect gate**: only when the initializer is provably side-effect-free (a literal/regex/pure expression — never a call/`await`/`new`), and **never a function parameter**.
- **`unused-params`** — silences unused parameters by **prefixing `_`** (the convention `tsc`/eslint ignore) — never removes them (that would change the signature), and skips destructured props.
- **`lint-fix`** — applies the project linter's **autofixable rules only** (`eslint --fix`, `ruff --fix`, …), bounded to the focus area, never a fixer that rewrites logic.
- **`dep-bump`** — bumps **one** dependency a patch/minor (never major) and ships only if the **full test suite** passes (blocks if the project has no tests).

The scope (and an optional path + `--dry-run` preview) goes in the prompt:

```bash
qodex schedule add --name nightly-tidy --cron "0 4 * * *" --recipe maintain \
  --prompt "unused-imports src/" --deliver telegram:<your-chat-id>
# 4am: prove-unused → remove → verify → PR for your review (or 🧾 blocked).
qodex schedule add --name preview --cron "@weekly" --recipe maintain --prompt "dead-code --dry-run"
# --dry-run: lists what it WOULD remove, changes nothing.
```

**Proof-carrying autonomy — every run comes with a receipt.** An unattended action is only trustworthy if you can *audit* it. Each run emits a structured **trust receipt** — what it set out to do, **which checks ran and whether they passed**, the files it touched, and the PR it opened (or why it didn't). Crucially, the hard facts are **measured by QodeX, not claimed by the model**: the `filesChanged` come from a real `git diff` and the `verification` entries from the checkers the agent loop *actually ran* — written out by QodeX itself, so the model can't fabricate a green receipt. The runner captures it, stores it, and leads the chat message with it:

```text
✅ QodeX schedule: nightly-flaky-fix
done in 274s

🧾 Receipt
status: ✅ opened
PR: https://github.com/you/app/pull/318
verified: ✓ npm test · ✓ tsc
files: src/auth/session.ts, test/auth.test.ts
```

```bash
qodex schedule runs <id>        # each run, with its receipt verdict (🧾 opened/blocked + PR)
qodex schedule receipt <id>     # the full receipt of the latest run
```

So "the agent did X overnight" stops being a claim and becomes a **checkable record** — the half a cron-wrapped chatbot structurally can't produce, because it never verified in the first place.

**Adopting maintain on your repo?** [docs/ADOPTION.md](docs/ADOPTION.md) has the 10-minute setup, a rollout ladder from `--dry-run` to `dep-bump`, and **real merged results** from running it on this very repository ([#62](https://github.com/QodeXcli/QodeX/pull/62): 6 unused imports removed · [#64](https://github.com/QodeXcli/QodeX/pull/64): 4 consts removed, 6 safely blocked by the side-effect gate). Show your team with `qodex maintain-demo` (interactive) / `--markdown` / `--pdf`.

## Architecture notes

- **One agent loop** with per-task budget caps (tokens / cost / wall-clock / iterations), a consecutive-failure circuit breaker, and auto-recovery.
- **Capability-tiered system prompt** — frontier models get a compressed prompt; weak/local models keep the full guidance they depend on (cache-safe per session).
- **Per-tool permissions** — read-only tools auto-approved; mutating tools ask once; "allow once / session / pattern / always" picker.
- **Code-graph index** — Tree-sitter-backed, persists to `.qodex/codegraph.db`, incremental.
- **Persistent memory** — sessions, messages, scoped (project/user) facts, and a per-project worklog in `~/.qodex/sessions.db`; episodic task-memory in `~/.qodex/episodes/`; curated rules in `QODEX.md`; a human-readable **Markdown mirror** (`/memory export|import`) and a budget-aware **Light Memory Mode** over the same store. All local, all under `~/.qodex/`.
- **Chat gateway** — one transport-agnostic bot core (Telegram / Discord / Slack adapters are thin) with throttled streaming, one-turn-per-chat queueing, inline-button approvals, deny-by-default auth, and **Living Artifact cards** with vision review. Bot asks share the **Operator Hub** with the TUI on **per-conversation lanes**, so a parked Telegram approval cannot starve `[bg1]`.
- **Named profiles** — `--profile` / `QODEX_PROFILE` last-word overlays (`~/.qodex/profiles/<name>.yaml`). Not `-p`.
- **Execution runtime** — `runtime.backend: local | docker`. Docker is process isolation for `shell`, not a second agent. Hub stays I/O; git sandbox stays branches.
- **Multi-provider router** — Ollama, LM Studio, Anthropic, OpenAI, Gemini, DeepSeek, OpenRouter all first-class.
- **ESM strict** throughout; **hooks** (pre/post-tool) for guardrails or instrumentation.

## Why local-first

- **No data leaves your machine** when running Ollama / LM Studio — useful for proprietary codebases.
- **Faster iteration** — no network latency per tool call.
- **Works offline** — `/network` tells you what's reachable.
- **$0 to run** if you have the hardware; cloud providers are opt-in per role (e.g. sub-agents on Claude, vision on GPT).
- **When you *do* go remote, the blast radius is a container** — not your home directory. That is the only honest way to put a coding agent on a phone.

## Status

Active development. The built-in tool set and the guardrail layer are stable; expect more MCP integrations and permission-UX polish. Issues and PRs welcome.

## License

Apache License 2.0 — see [LICENSE](LICENSE) and [NOTICE](NOTICE).

Copyright 2026 7 Seven.

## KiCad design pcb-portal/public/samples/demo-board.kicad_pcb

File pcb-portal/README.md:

# QodeX PCB — website, customer portal and 3D Studio

The public website and ordering portal for the QodeX PCB routing service. **Routing does not run on the website** — the QodeX engine runs offline on your own workstation. The site takes care of everything around it:

- **Marketing site** (server-rendered, SEO-ready): home, how it works, 3D Studio, six use-case pages, KiCad integration, pricing estimator, evidence library, docs & DFM academy, trust & security, about, careers, contact, legal. Canonical URLs, Open Graph, JSON-LD, `sitemap.xml`, `robots.txt` and `llms.txt` are generated.
- **Ordering:** customers drop a `.kicad_pcb` (plus any project files). The board is parsed in the browser for an instant 3D preview and quote, and parsed again on the server, whose geometry is authoritative for pricing.
- **Payments in USD:** Stripe Checkout (cards, Apple Pay, Google Pay, Link) and PayPal (Orders v2). Customers choose at checkout. Payments are verified server-to-server, callbacks are idempotent, and a signed Stripe webhook covers customers who close the tab. Printable receipts in the portal.
- **3D Studio / viewer:** `.kicad_pcb` (KiCad 5–9), `.glb`, `.gltf`, `.stl`, `.obj`, `.wrl`. Layer toggles, solder-mask transparency, exploded stack, **inspect** (hover to identify pads/vias/tracks/parts, click to highlight a whole net with its routed length), **measure** (distance, ΔX/ΔY, mils), auto-rotate, screenshot, fullscreen.
- **Customer portal:** dashboard, new order, order detail (status steps, deliverables with 3D view, engineer message thread, activity log), billing & receipts, account settings.
- **Admin panel:** order queue with stats and search, pricing/status/internal notes, deliverable upload (optionally marking the order delivered), customers, contact-form inbox, tariff editor.

## Your workflow

```
Customer uploads board + pays (USD) ─► Admin queue: "Paid — queued"
                                         │
      download customer files ◄──────────┘
      route on your workstation with the QodeX engine
      upload deliverables (.kicad_pcb, .glb, gerber zip, dossier.pdf) + tick "Mark as delivered"
                                         │
Customer: 3D review, download, confirm ◄─┘
```

Generate a GLB from a routed board with KiCad 8/9: `kicad-cli pcb export glb -o board.glb board.kicad_pcb` (the `.kicad_pcb` itself also opens directly in the viewer).

## Setup

Requires Node.js 20+.

```bash
cd pcb-portal
npm install
cp .env.example .env      # then edit it
npm start                 # http://localhost:8787
```

| Variable | Purpose |
|---|---|
| `PUBLIC_BASE_URL` | Public URL of the site; payment providers redirect back here. Use `https://` in production. |
| `SITE_NAME`, `COMPANY_NAME`, `SUPPORT_EMAIL` | Shown in the header, footer, receipts and legal pages. |
| `ADMIN_EMAIL`, `ADMIN_PASSWORD` | First admin account (created on startup). Or later: `npm run create-admin -- email password "Name"`. |
| `PAYMENT_PROVIDERS` | Comma-separated: `stripe`, `paypal`, `mock`. `mock` is a development-only test checkout. |
| `STRIPE_SECRET_KEY`, `STRIPE_WEBHOOK_SECRET` | Stripe API key and the signing secret of the webhook endpoint below. |
| `PAYPAL_CLIENT_ID`, `PAYPAL_CLIENT_SECRET`, `PAYPAL_SANDBOX` | PayPal REST app credentials; `PAYPAL_SANDBOX=true` for testing. |
| `DATA_DIR` | SQLite database and uploaded files. **Back this folder up.** |
| `MAX_UPLOAD_MB`, `TRUST_PROXY` | Upload limit; set `TRUST_PROXY=true` behind nginx / Cloudflare. |

### Stripe

1. Create a restricted or secret key and set `STRIPE_SECRET_KEY`.
2. Add a webhook endpoint `https://<your-domain>/api/payments/stripe/webhook` for `checkout.session.completed` and `checkout.session.async_payment_succeeded`, and put its signing secret in `STRIPE_WEBHOOK_SECRET`.
3. Enable Apple Pay / Google Pay in the Stripe dashboard if you want them offered in Checkout.

### PayPal

Create a REST app in the PayPal developer dashboard, set `PAYPAL_CLIENT_ID` / `PAYPAL_CLIENT_SECRET`, and test with `PAYPAL_SANDBOX=true` before switching to live credentials.

### Pricing

After signing in as admin, open **Pricing** and set your tariffs (the defaults are starting points). Turn off automatic quotes if you prefer to price every order by hand: orders then wait in "Awaiting quote" until you set a price. Off-site payments (wire transfer, invoice) can be recorded by setting the order status to "Paid".

### Production

- Run behind a TLS reverse proxy (nginx, Caddy, Cloudflare Tunnel). With an `https://` base URL, cookies become `Secure` and HSTS is sent.
- Allow request bodies at least as large as `MAX_UPLOAD_MB` in the proxy.
- `NODE_ENV=production npm start` under pm2 / systemd / launchd.
- Remove `mock` from `PAYMENT_PROVIDERS`.
- Have the legal pages (`views/site/legal.html`) reviewed by counsel for your jurisdiction and company.

## Order statuses

Awaiting quote → Awaiting payment → Paid — queued → In progress → Delivered → Completed (or Cancelled).

## Security

- Files are stored under random names outside any public directory and served only through `/api/files/:id` to the order owner and admins.
- scrypt password hashing; HttpOnly + SameSite session cookies; CSRF guard via a required custom header; rate limits on auth and contact endpoints; strict CSP with no third-party scripts.
- Orders are marked paid only after server-side verification with the provider (amount, currency and reference must match). Repricing an order cancels any open checkout. Internal admin notes are never sent to customers.
- Upload extension allow-list, size cap and SHA-256 per file.

## Layout

```
pcb-portal/
├── server/
│   ├── app.js           routes, page rendering, SEO files, Stripe webhook, CSP
│   ├── layout.js        server-side layout (header, footer, sidebar, meta, JSON-LD)
│   ├── content.js       use-case page content
│   ├── routes/          api.js (auth, orders, files, payments, contact) · admin.js
│   ├── payments/        stripe.js · paypal.js · service.js (verify + finalise) · index.js (mock)
│   └── pricing.js       spec validation and USD quote calculation
├── views/               site/, portal/, admin/ page fragments
├── public/
│   ├── css/app.css      design system
│   ├── js/viewer/       kicad-parser.js (shared with the server) · kicad-scene.js · viewer.js
│   ├── js/pages/        one script per page
│   └── samples/         open demo board (scripts/make-demo-board.js)
└── test/                node --test (npm test)
```

## Tests

```bash
npm test
```

Covers the KiCad parser (KiCad 5 legacy through 9, rotations, THT/NPTH, arcs, nets), pricing, every public page (rendered, no unfilled placeholders), the full order/payment/delivery API including access control, the contact inbox, and PayPal and Stripe flows (including webhook signatures) against stubbed providers.

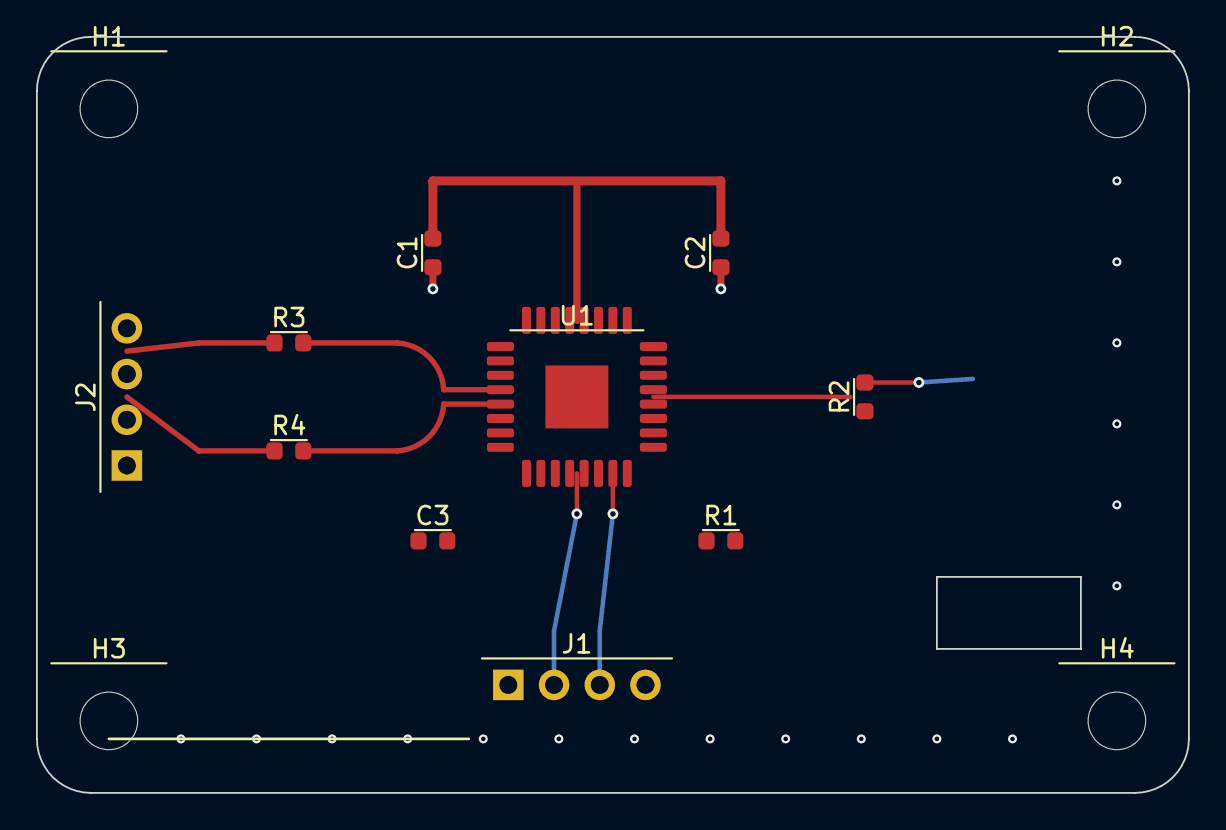
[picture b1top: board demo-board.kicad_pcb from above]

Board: 4 copper layers, 64.0 x 42.0 mm, 15 parts (1 on the bottom side), 10 nets.

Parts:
C1, C2: 100nF; C_0603_1608Metric
C3: 4.7uF; C_0603_1608Metric
D1: GREEN; LED_0805_2012Metric
H1, H2, H3, H4: M3; MountingHole_3.2mm_M3
J1: SWD; PinHeader_1x04_P2.54mm_Vertical
J2: USB; PinHeader_1x04_P2.54mm_Vertical
R1: 10k; R_0603_1608Metric
R2: 330R; R_0603_1608Metric
R3, R4: 22R; R_0603_1608Metric
U1: STM32G031K8; LQFP-32_7x7mm_P0.8mm

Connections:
+3V3: C1.1, C2.1, C3.1, J1.1, R1.2, U1.10, U1.20, U1.30
GND: C1.2, C2.2, C3.2, D1.2, J1.4, J2.4, R2.2, U1.1, U1.11, U1.21, U1.31, U1.33
LED: D1.1, R2.1, U1.3, U1.13, U1.23
NRST: R1.1, U1.2, U1.12, U1.22, U1.32
RX: U1.5, U1.15, U1.25
SWCLK: J1.3, U1.9, U1.19, U1.29
SWDIO: J1.2, U1.8, U1.18, U1.28
TX: U1.4, U1.14, U1.24
USB_D+: J2.3, R3.1, R3.2, U1.7, U1.17, U1.27
USB_D-: J2.2, R4.1, R4.2, U1.6, U1.16, U1.26
